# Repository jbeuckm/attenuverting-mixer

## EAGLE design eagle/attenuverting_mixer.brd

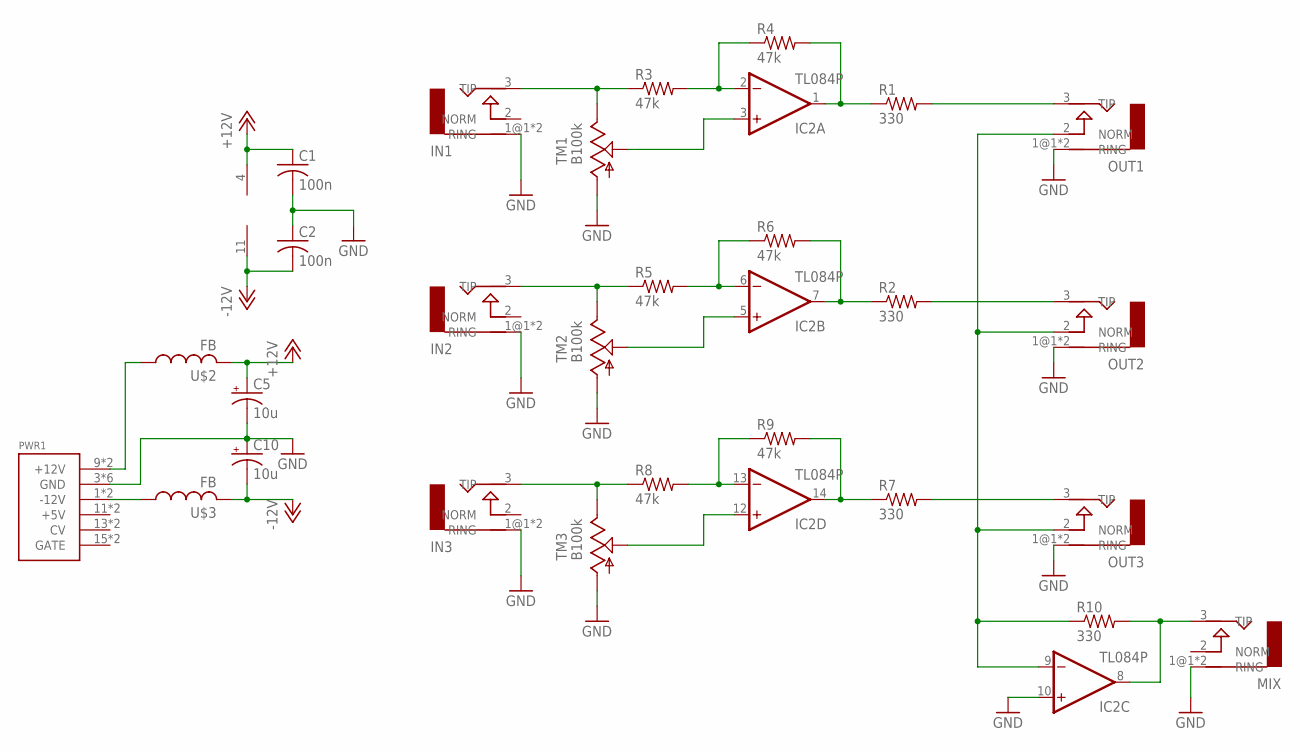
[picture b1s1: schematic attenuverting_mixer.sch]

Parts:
C1, C2: 100n; C1206
C5, C10: 10u; B45181A
IC2: TL084P; DIL14
IN1, IN2, IN3: AUDIO-JACKERTHENVAR; ERTHENVAR-JACK
MIX: AUDIO-JACKERTHENVAR; ERTHENVAR-JACK
OUT1, OUT2, OUT3: AUDIO-JACKERTHENVAR; ERTHENVAR-JACK
PWR1: POWER; POWER_16
R1, R2, R7, R10: 330; 0207/7
R3, R4, R5, R6, R8, R9: 47k; 0207/7
TM1, TM2, TM3: B100k; SLIDEPOT-60
U$2, U$3: FB

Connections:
+12V: C1.1, C5.+, IC2.4 (V+), U$2.P$2 (2)
-12V: C2.2, C10.-, IC2.11 (V-), U$3.P$2 (2)
GND: C1.2, C2.1, C5.-, C10.+, IC2.10 (+IN), IN1.1@1 (RING), IN1.1@2 (RING), IN2.1@1 (RING), IN2.1@2 (RING), IN3.1@1 (RING), IN3.1@2 (RING), MIX.1@1 (RING), MIX.1@2 (RING), OUT1.1@1 (RING), OUT1.1@2 (RING), OUT2.1@1 (RING), OUT2.1@2 (RING), OUT3.1@1 (RING), OUT3.1@2 (RING), PWR1.3 (GND), PWR1.4 (GND), PWR1.5 (GND), PWR1.6 (GND), PWR1.7 (GND), PWR1.8 (GND), TM1.A, TM2.A, TM3.A
unnamed: IN2.3 (TIP), R5.1, TM2.B
unnamed: IN1.3 (TIP), R3.1, TM1.B
unnamed: IC2.2 (-IN), R3.2, R4.1
unnamed: IC2.1 (OUT), R1.1, R4.2
unnamed: OUT1.3 (TIP), R1.2
unnamed: IC2.3 (+IN), TM1.WIPER
unnamed: IC2.6 (-IN), R5.2, R6.1
unnamed: IC2.7 (OUT), R2.1, R6.2
unnamed: OUT2.3 (TIP), R2.2
unnamed: IC2.5 (+IN), TM2.WIPER
unnamed: PWR1.9 (+12V), PWR1.10 (+12V), U$2.P$1 (1)
unnamed: IN3.3 (TIP), R8.1, TM3.B
unnamed: IC2.13 (-IN), R8.2, R9.1
unnamed: IC2.14 (OUT), R7.1, R9.2
unnamed: OUT3.3 (TIP), R7.2
unnamed: IC2.12 (+IN), TM3.WIPER
unnamed: PWR1.1 (-12V), PWR1.2 (-12V), U$3.P$1 (1)
unnamed: IC2.9 (-IN), OUT1.2 (NORM), OUT2.2 (NORM), OUT3.2 (NORM), R10.1
unnamed: IC2.8 (OUT), MIX.3 (TIP), R10.2

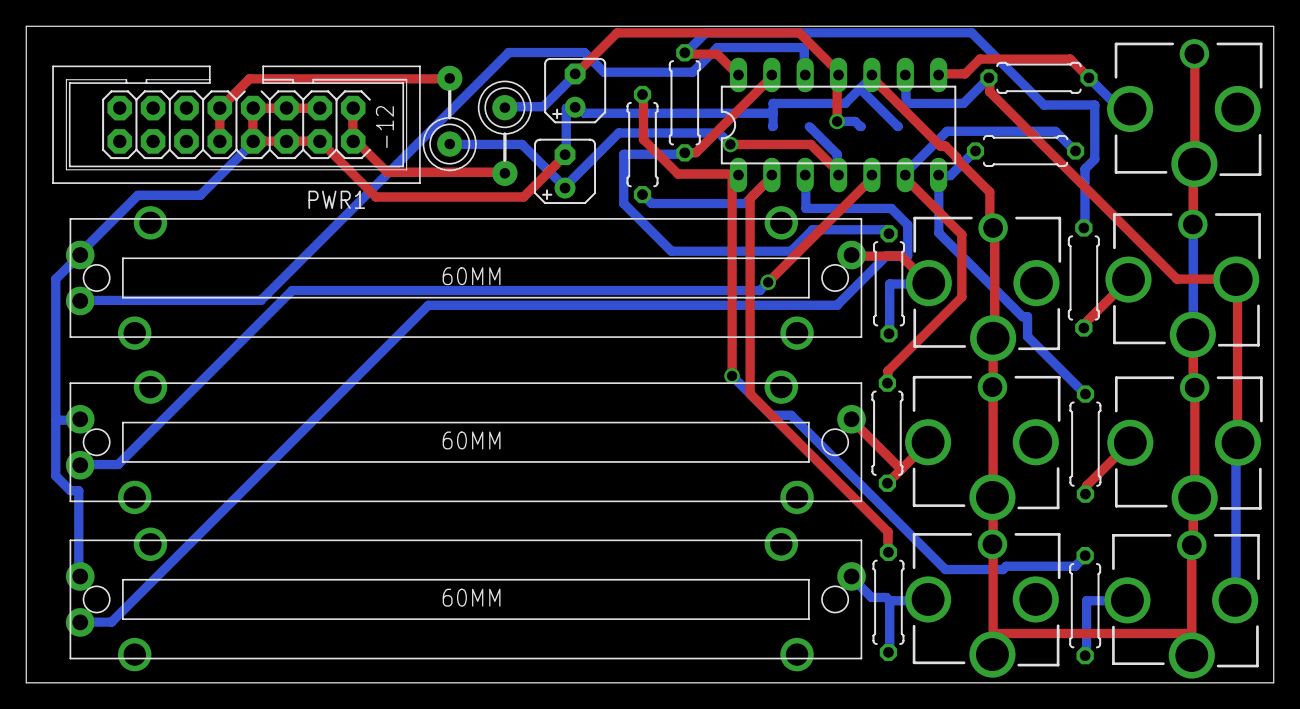
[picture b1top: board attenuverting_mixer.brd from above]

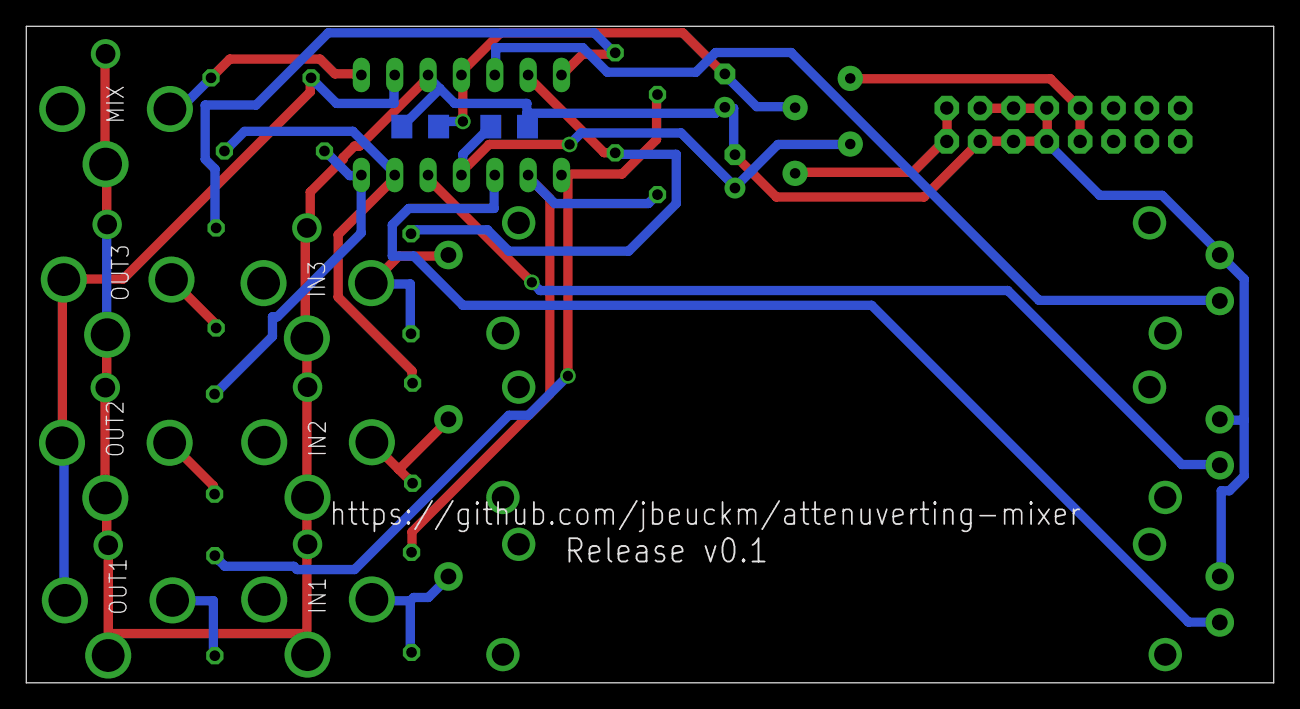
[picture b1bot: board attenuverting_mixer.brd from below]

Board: 2 copper layers, 95.0 x 50.0 mm, 28 parts (2 on the bottom side), 22 nets.

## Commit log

2018-01-28 label tweaks
2018-01-28 readme with images
